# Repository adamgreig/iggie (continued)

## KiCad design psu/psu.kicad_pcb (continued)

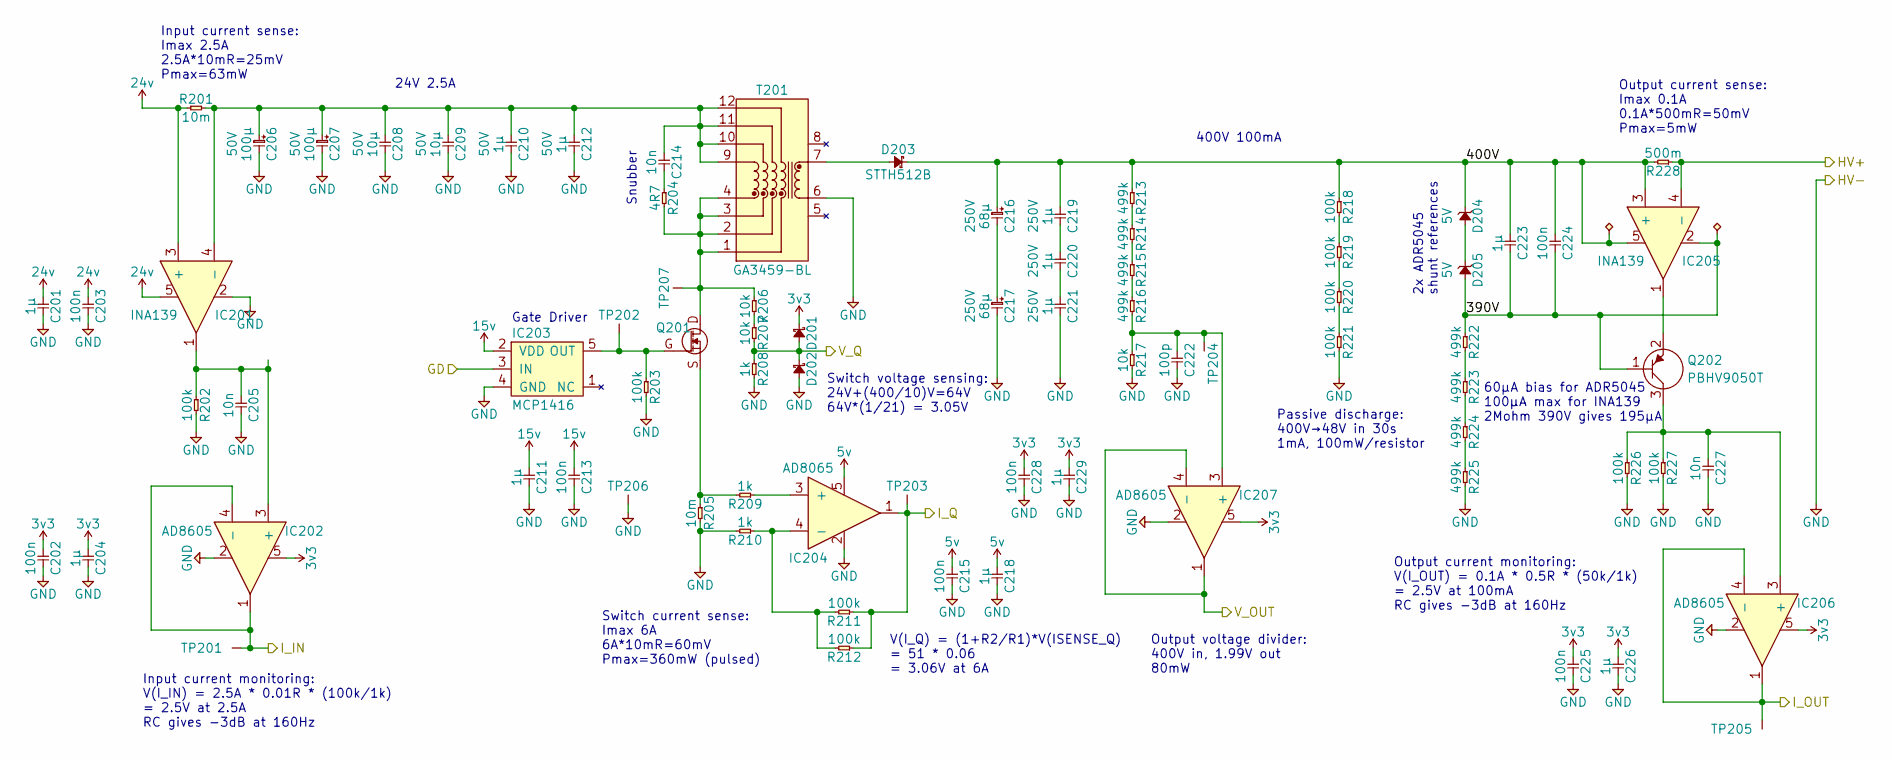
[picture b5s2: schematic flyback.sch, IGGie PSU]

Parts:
C201, C210, C211, C212: 1µ; 1206; Voltage 50V; Farnell 1759454
C202, C203, C213, C215, C224, C225, C228: 100n; 0603; Voltage 50V; Farnell 2320803
C204, C218, C223, C226, C229: 1µ; 0603; Voltage 16V; Farnell 2320814
C205, C227: 10n; 0805; Voltage 25V; Farnell 1457736
C206, C207: 100µ; PANASONIC-SMDCAP-G; Voltage 50V; Farnell 2079271
C208, C209: 10µ; 1210; Voltage 50V; Farnell 2781426
C214: 10n; 1206; Voltage 50V; Farnell 2896776
C216, C217: 68µ; PANASONIC-SMDCAP-K; Voltage 250V; Farnell 2326343
C219, C220, C221: 1µ; 2220; Voltage 250V; Farnell 1828845
C222: 100p; 0603; Voltage 50V; Farnell 9406115
D201, D202: NTS245SFT1G; SOD-123; Farnell 2473418
D203: STTH512B; DPAK_DIODE; Farnell 2344055
D204, D205: ADR5045; SOT-23; Voltage 5V; Farnell 2460166
IC201, IC205: INA139; SOT-23-5; Farnell 1470398
IC202, IC206, IC207: AD8605; SOT-23-5; Farnell 1838870
IC203: MCP1416; SOT-23-5; Farnell 1630421
IC204: AD8065; SOT-23-5; Farnell 2376729
Q201: STB45N60DM2AG; D2PAK_GDS; Farnell 3129762
Q202: PBHV9050T; SOT-23; Voltage 500V; Farnell 1829318
R201, R205: 10m; 1206; Farnell 2079442
R202, R203, R211, R212, R226, R227: 100k; 0603; Voltage 50V; Farnell 2447226
R204: 4R7; 1206; Voltage 50V; Farnell 2447524
R206, R207, R217: 10k; 0603; Voltage 50V; Farnell 2447230
R208, R209, R210: 1k; 0603; Voltage 50V; Farnell 2447272
R213, R214, R215, R216, R222, R223, R224, R225: 499k; 1206; Voltage 200V; Farnell 2695162
R218, R219, R220, R221: 100k; 1206; Voltage 200V; Farnell 2447453
R228: 500m; 1206; Farnell 1717875
T201: GA3459-BL; Farnell 2458040
TP201, TP204, TP205: TESTPAD
TP202, TP203, TP206, TP207: TESTPAD; KEYSTONE5016

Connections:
3v3: C202.1, C204.1, C225.1, C226.1, C228.1, C229.1, D201.1, IC202.5, IC206.5, IC207.5; also elsewhere on the board
5v: C215.1, C218.1, IC204.5; also elsewhere on the board
15v: C211.1, C213.1, IC203.2 (VDD); also elsewhere on the board
24v: C201.1, C203.1, IC201.3 (+), IC201.5, R201.1; also elsewhere on the board
/Flyback/390V: C223.2, C224.2, D205.2, IC205.2, Q202.1 (B), R222.1
/Flyback/400V: C216.2, C219.1, C223.1, C224.1, D203.1, D204.1, IC205.3 (+), IC205.5, R213.1, R218.1, R228.2
/Flyback/HV+: IC205.4 (-), R228.1; also elsewhere on the board
/GD: IC203.3 (IN); also elsewhere on the board
/I_IN: IC202.1, IC202.4 (-), TP201.1; also elsewhere on the board
/I_OUT: IC206.1, IC206.4 (-), TP205.1; also elsewhere on the board
/I_Q: IC204.1, R211.1, R212.1, TP203.1; also elsewhere on the board
/VOUT_MON: IC207.1, IC207.4 (-); also elsewhere on the board
/V_Q: D201.2, D202.1, R207.2, R208.1; also elsewhere on the board
GND: C201.2, C202.2, C203.2, C204.2, C205.2, C206.1, C207.1, C208.2, C209.2, C210.2, C211.2, C212.2, C213.2, C215.2, C217.1, C218.2, C221.2, C222.2, C225.2, C226.2, C227.2, C228.2, C229.2, D202.2, IC201.2, IC202.2, IC203.4 (GND), IC204.2, IC206.2, IC207.2, R202.2, R203.2, R205.2, R208.2, R210.2, R217.2, R221.2, R225.2, R226.2, R227.2, T201.6, TP206.1; also elsewhere on the board
unnamed: C205.1, IC201.1, IC202.3 (+), R202.1
unnamed: C206.2, C207.2, C208.1, C209.1, C210.1, C212.1, C214.1, IC201.4 (-), R201.2, T201.9, T201.10, T201.11, T201.12
unnamed: C214.2, R204.1
unnamed: C216.1, C217.2
unnamed: C219.2, C220.1
unnamed: C220.2, C221.1
unnamed: C222.1, IC207.3 (+), R216.2, R217.1, TP204.1
unnamed: C227.1, IC206.3 (+), Q202.3 (C), R226.1, R227.1
unnamed: D203.2, T201.7
unnamed: D204.2, D205.1
unnamed: IC203.5 (OUT), Q201.G, R203.1, TP202.1
unnamed: IC204.3 (+), R209.1
unnamed: IC204.4 (-), R210.1, R211.2, R212.2
unnamed: IC205.1, Q202.2 (E)
unnamed: Q201.D, R204.2, R206.1, T201.1, T201.2, T201.3, T201.4, TP207.1
unnamed: Q201.S, R205.1, R209.2
unnamed: R206.2, R207.1
unnamed: R213.2, R214.1
unnamed: R214.2, R215.1
unnamed: R215.2, R216.1
unnamed: R218.2, R219.1
unnamed: R219.2, R220.1
unnamed: R220.2, R221.1
unnamed: R222.2, R223.1
unnamed: R223.2, R224.1
unnamed: R224.2, R225.1

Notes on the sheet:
Switch current sense: Imax 6A 6A*10mR=60mV Pmax=360mW (pulsed)
Snubber
Passive discharge: 400V→48V in 30s 1mA, 100mW/resistor
Gate Driver
V(I_Q) = (1+R2/R1)*V(ISENSE_Q) = 51 * 0.06 = 3.06V at 6A
Input current monitoring: V(I_IN) = 2.5A * 0.01R * (100k/1k) = 2.5V at 2.5A RC gives -3dB at 160Hz
Output voltage divider: 400V in, 1.99V out 80mW
Output current monitoring: V(I_OUT) = 0.1A * 0.5R * (50k/1k) = 2.5V at 100mA RC gives -3dB at 160Hz
60µA bias for ADR5045 100µA max for INA139 2Mohm 390V gives 195µA
2x ADR5045 shunt references
24V 2.5A
400V 100mA
Switch voltage sensing: 24V+(400/10)V=64V 64V*(1/21) = 3.05V
Input current sense: Imax 2.5A 2.5A*10mR=25mV Pmax=63mW
Output current sense: Imax 0.1A 0.1A*500mR=50mV Pmax=5mW

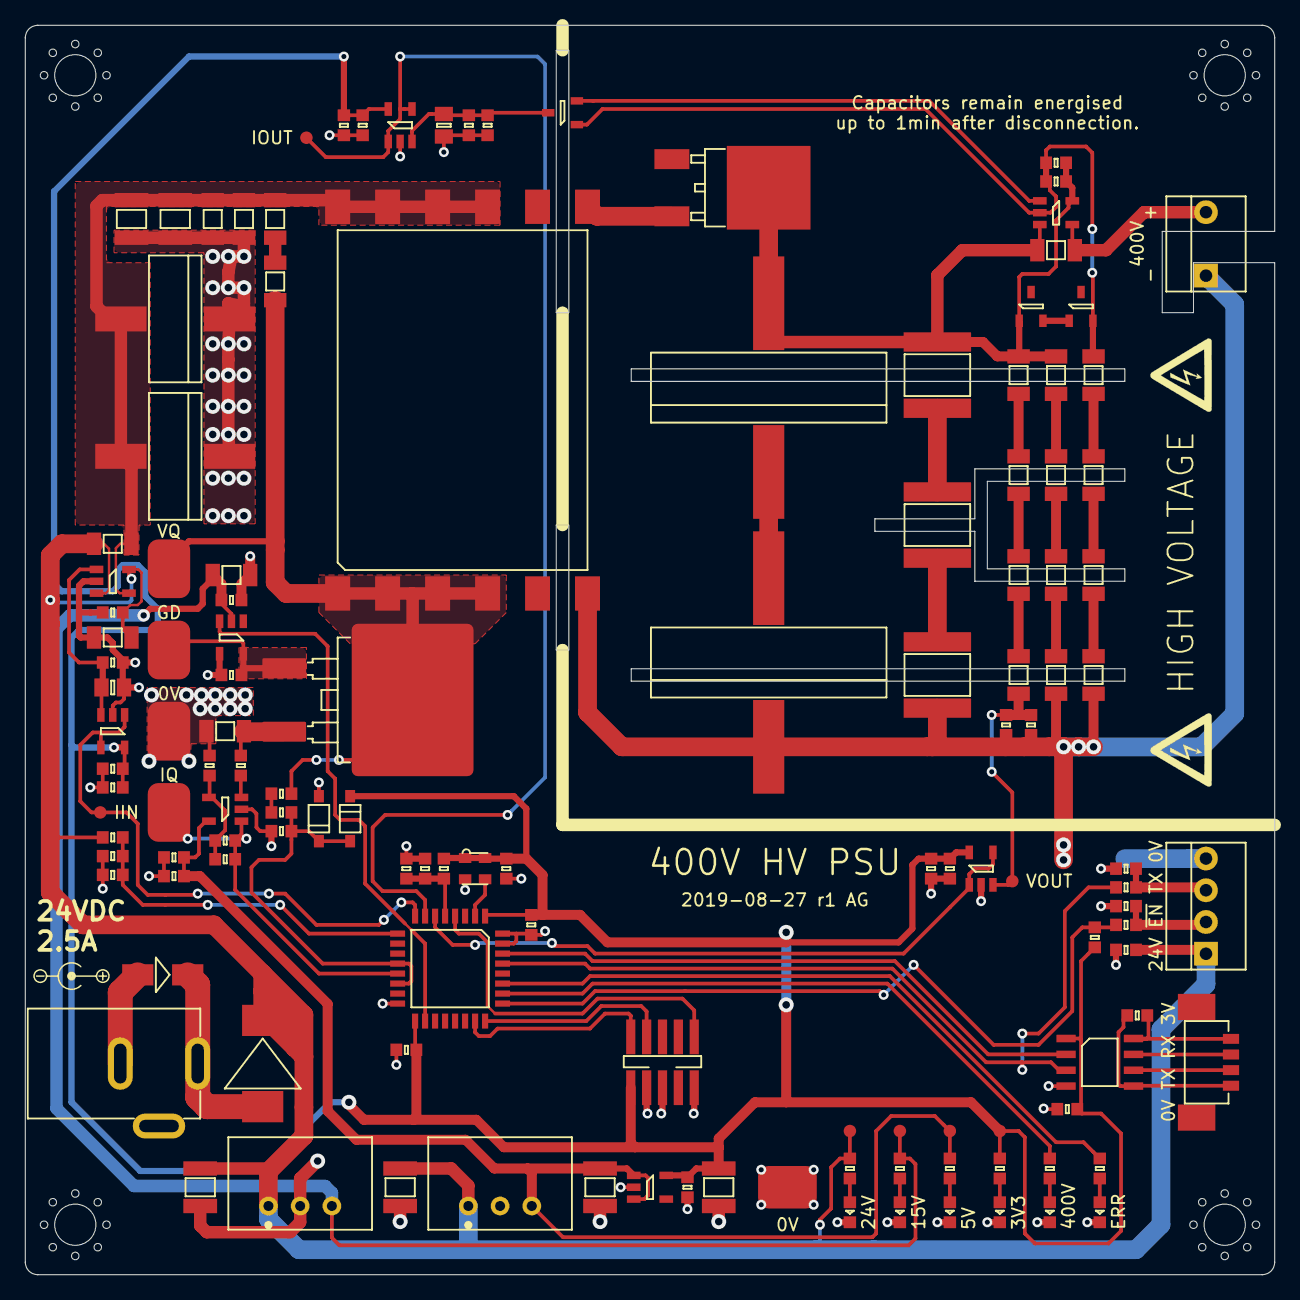
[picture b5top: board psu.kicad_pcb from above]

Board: 2 copper layers, 100.0 x 100.0 mm, 137 parts (0 on the bottom side), 64 nets.

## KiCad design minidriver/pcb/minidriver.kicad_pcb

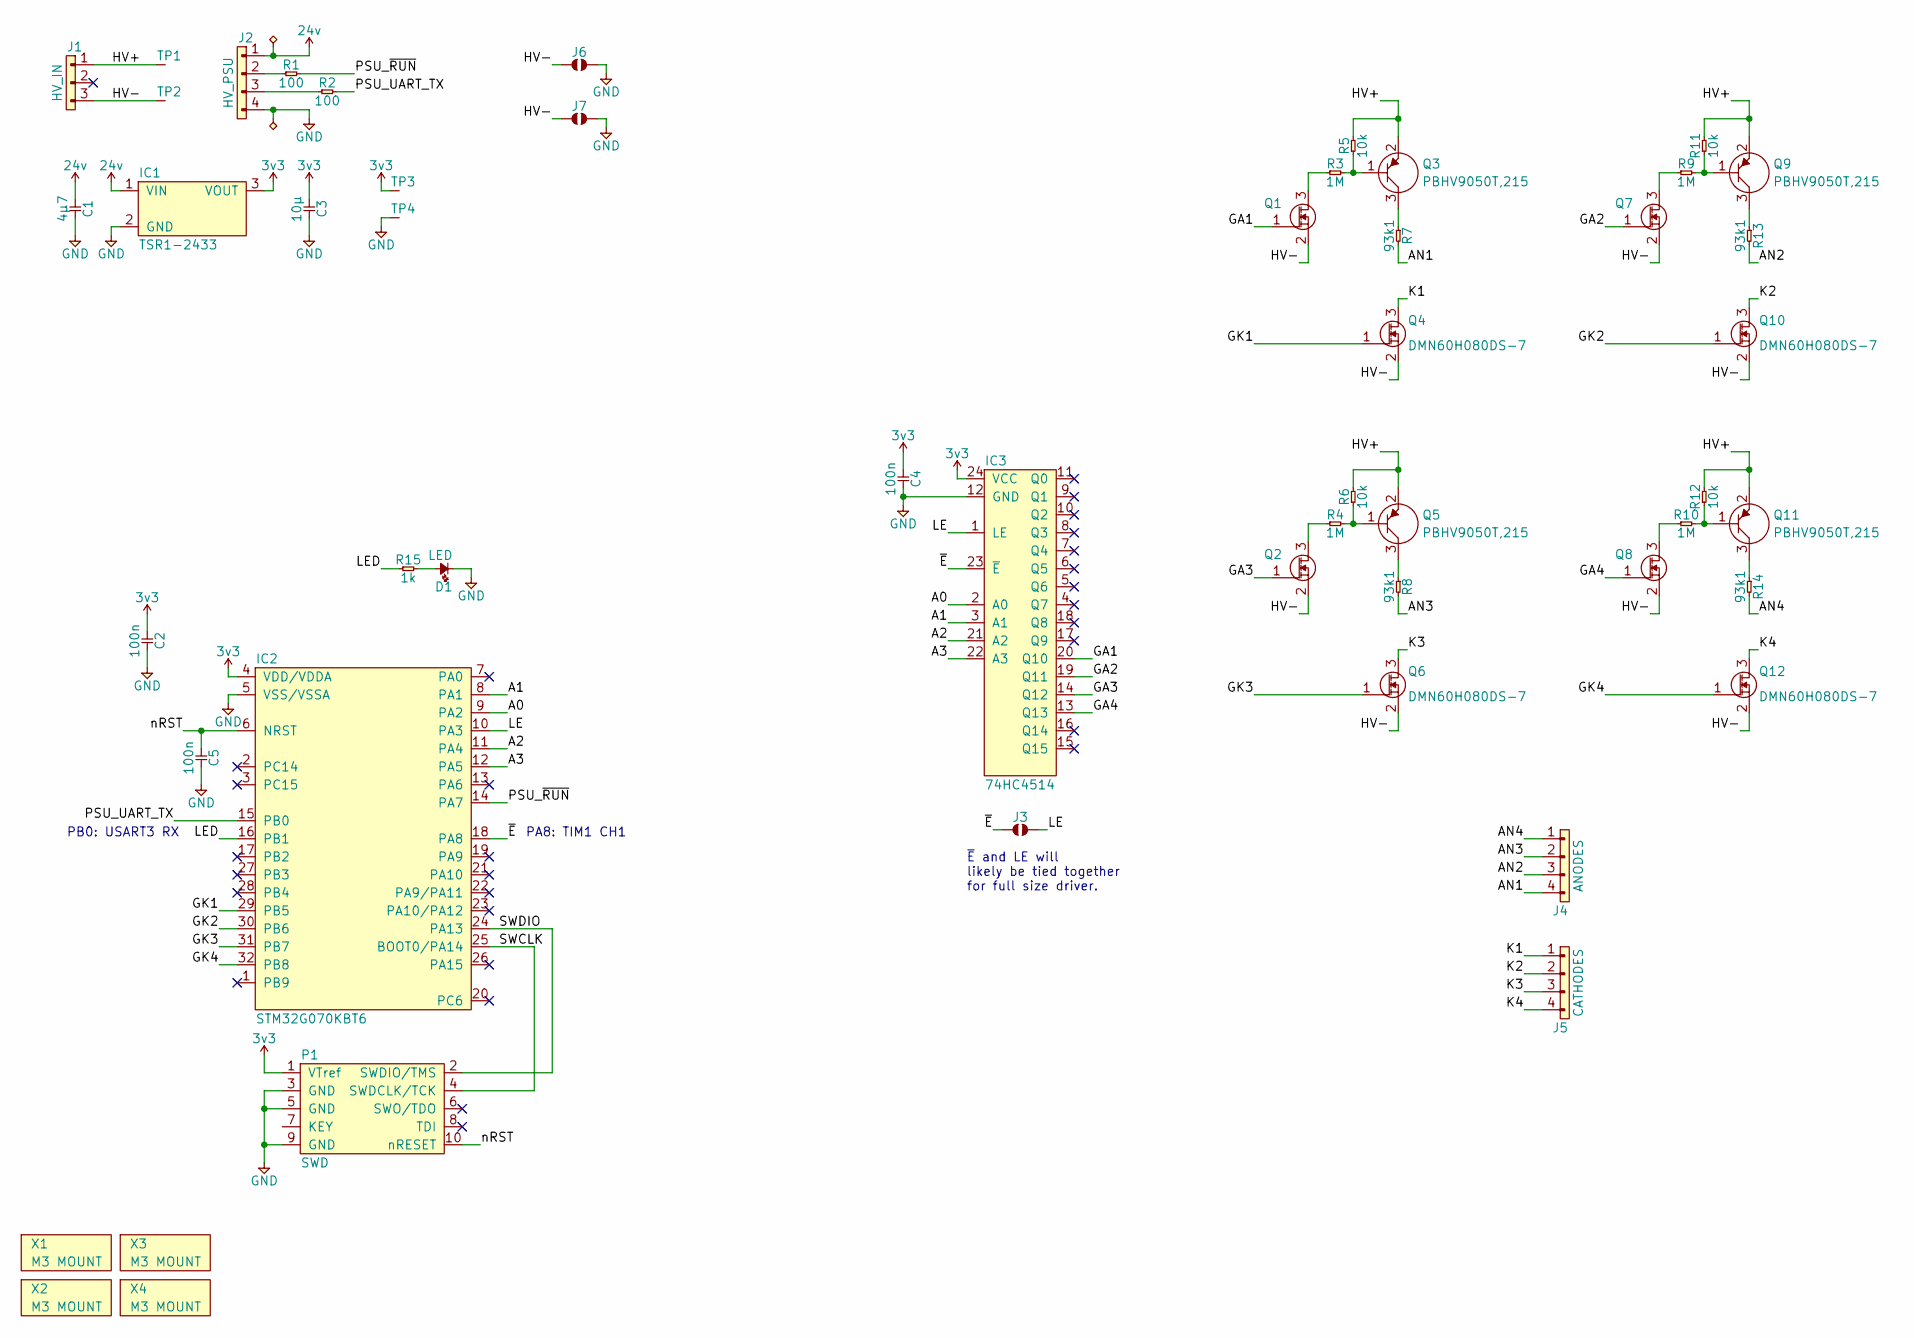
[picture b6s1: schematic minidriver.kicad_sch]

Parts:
C1: 4µ7; 1206; Voltage 50V; Farnell 2112859
C2, C4, C5: 100n; 0402; Voltage 16V; Farnell 2810260
C3: 10µ; 0603; Voltage 6.3V; Farnell 3013391
D1: LED; 0603-LED; Farnell 2290328
IC1: TSR1-2433; TSR1; Farnell 1696319
IC2: STM32G070KBT6; LQFP-32; Farnell 3365394
IC3: 74HC4514; SOIC-24-W; Farnell 2444987
J1: HV_IN; MOLEX-KK-254P-03; Farnell 1360131
J2: HV_PSU; MOLEX-KK-254P-04; Farnell 1360132
J3, J6, J7: SJ2
J4: ANODES; MOLEX-KK-254P-04; Farnell 1360132
J5: CATHODES; MOLEX-KK-254P-04; Farnell 1360132
P1: SWD; FTSH-105-01-L-DV-K; Farnell 2856437
Q1, Q2, Q4, Q6, Q7, Q8, Q10, Q12: DMN60H080DS-7; SOT-23; Farnell 3127344
Q3, Q5, Q9, Q11: PBHV9050T,215; SOT-23; Farnell 1829318
R1, R2: 100; 0402; Voltage 50V; Farnell 9239111
R3, R4, R9, R10: 1M; 1206; Voltage 500V; Farnell 1750877
R5, R6, R11, R12: 10k; 1206; Voltage 500V; Farnell 1750850
R7, R8, R13, R14: 93k1; 1206; Voltage 500V; Farnell 2327389
R15: 1k; 0402; Voltage 50V; Farnell 2331474
TP1, TP2: TESTPAD; KEYSTONE5016; Farnell 2292858
TP3: TESTPAD
TP4: TESTPAD; SIL-254P-01
X1, X2, X3, X4: M3 MOUNT; M3_MOUNT

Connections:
3v3: C2.1, C3.1, C4.1, IC1.3 (VOUT), IC2.4 (VDD/VDDA), IC3.24 (VCC), P1.1 (VTref), TP3.1 (TP)
24v: C1.1, IC1.1 (VIN), J2.1
/A0: IC2.9 (PA2), IC3.2 (A0)
/A1: IC2.8 (PA1), IC3.3 (A1)
/A2: IC2.11 (PA4), IC3.21 (A2)
/A3: IC2.12 (PA5), IC3.22 (A3)
/AN1: J4.4, R7.2
/AN2: J4.3, R13.2
/AN3: J4.2, R8.2
/AN4: J4.1, R14.2
/GA1: IC3.20 (Q10), Q1.1 (G)
/GA2: IC3.19 (Q11), Q7.1 (G)
/GA3: IC3.14 (Q12), Q2.1 (G)
/GA4: IC3.13 (Q13), Q8.1 (G)
/GK1: IC2.29 (PB5), Q4.1 (G)
/GK2: IC2.30 (PB6), Q10.1 (G)
/GK3: IC2.31 (PB7), Q6.1 (G)
/GK4: IC2.32 (PB8), Q12.1 (G)
/HV+: J1.1, Q3.2 (E), Q5.2 (E), Q9.2 (E), Q11.2 (E), R5.2, R6.2, R11.2, R12.2, TP1.1 (TP)
/HV-: J1.3, J6.1, J7.1, Q1.2 (S), Q2.2 (S), Q4.2 (S), Q6.2 (S), Q7.2 (S), Q8.2 (S), Q10.2 (S), Q12.2 (S), TP2.1 (TP)
/K1: J5.1, Q4.3 (D)
/K2: J5.2, Q10.3 (D)
/K3: J5.3, Q6.3 (D)
/K4: J5.4, Q12.3 (D)
/LE: IC2.10 (PA3), IC3.1 (LE), J3.2
/LED: IC2.16 (PB1), R15.1
/PSU_UART_TX: IC2.15 (PB0), R2.2
/PSU_~RUN: IC2.14 (PA7), R1.2
/SWCLK: IC2.25 (BOOT0/PA14), P1.4 (SWDCLK/TCK)
/SWDIO: IC2.24 (PA13), P1.2 (SWDIO/TMS)
/nRST: C5.1, IC2.6 (NRST), P1.10 (nRESET)
/~E: IC2.18 (PA8), IC3.23 (~E), J3.1
GND: C1.2, C2.2, C3.2, C4.2, C5.2, D1.1, IC1.2 (GND), IC2.5 (VSS/VSSA), IC3.12 (GND), J2.4, J6.2, J7.2, P1.3 (GND), P1.5 (GND), P1.9 (GND), TP4.1 (TP)
unnamed: D1.2, R15.2
unnamed: J2.2, R1.1
unnamed: J2.3, R2.1
unnamed: Q1.3 (D), R3.1
unnamed: Q2.3 (D), R4.1
unnamed: Q3.1 (B), R3.2, R5.1
unnamed: Q3.3 (C), R7.1
unnamed: Q5.1 (B), R4.2, R6.1
unnamed: Q5.3 (C), R8.1
unnamed: Q7.3 (D), R9.1
unnamed: Q8.3 (D), R10.1
unnamed: Q9.1 (B), R9.2, R11.1
unnamed: Q9.3 (C), R13.1
unnamed: Q11.1 (B), R10.2, R12.1
unnamed: Q11.3 (C), R14.1
no_connect_49: IC2.1 (PB9)
no_connect_50: IC2.13 (PA6)
no_connect_51: IC2.17 (PB2)
no_connect_52: IC2.19 (PA9)
no_connect_53: IC2.2 (PC14)
no_connect_54: IC2.20 (PC6)
no_connect_55: IC2.21 (PA10)
no_connect_56: IC2.22 (PA9/PA11)
no_connect_57: IC2.23 (PA10/PA12)
no_connect_58: IC2.26 (PA15)
no_connect_59: IC2.27 (PB3)
no_connect_60: IC2.28 (PB4)
no_connect_61: IC2.3 (PC15)
no_connect_62: IC2.7 (PA0)
no_connect_63: IC3.10 (Q2)
no_connect_64: IC3.11 (Q0)
no_connect_65: IC3.15 (Q15)
no_connect_66: IC3.16 (Q14)
no_connect_67: IC3.17 (Q9)
no_connect_68: IC3.18 (Q8)
no_connect_69: IC3.4 (Q7)
no_connect_70: IC3.5 (Q6)
no_connect_71: IC3.6 (Q5)
no_connect_72: IC3.7 (Q4)
no_connect_73: IC3.8 (Q3)
no_connect_74: IC3.9 (Q1)
no_connect_76: P1.6 (SWO/TDO)
no_connect_77: P1.8 (TDI)

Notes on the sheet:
PB0: USART3 RX
PA8: TIM1 CH1
~E~ and LE will likely be tied together for full size driver.

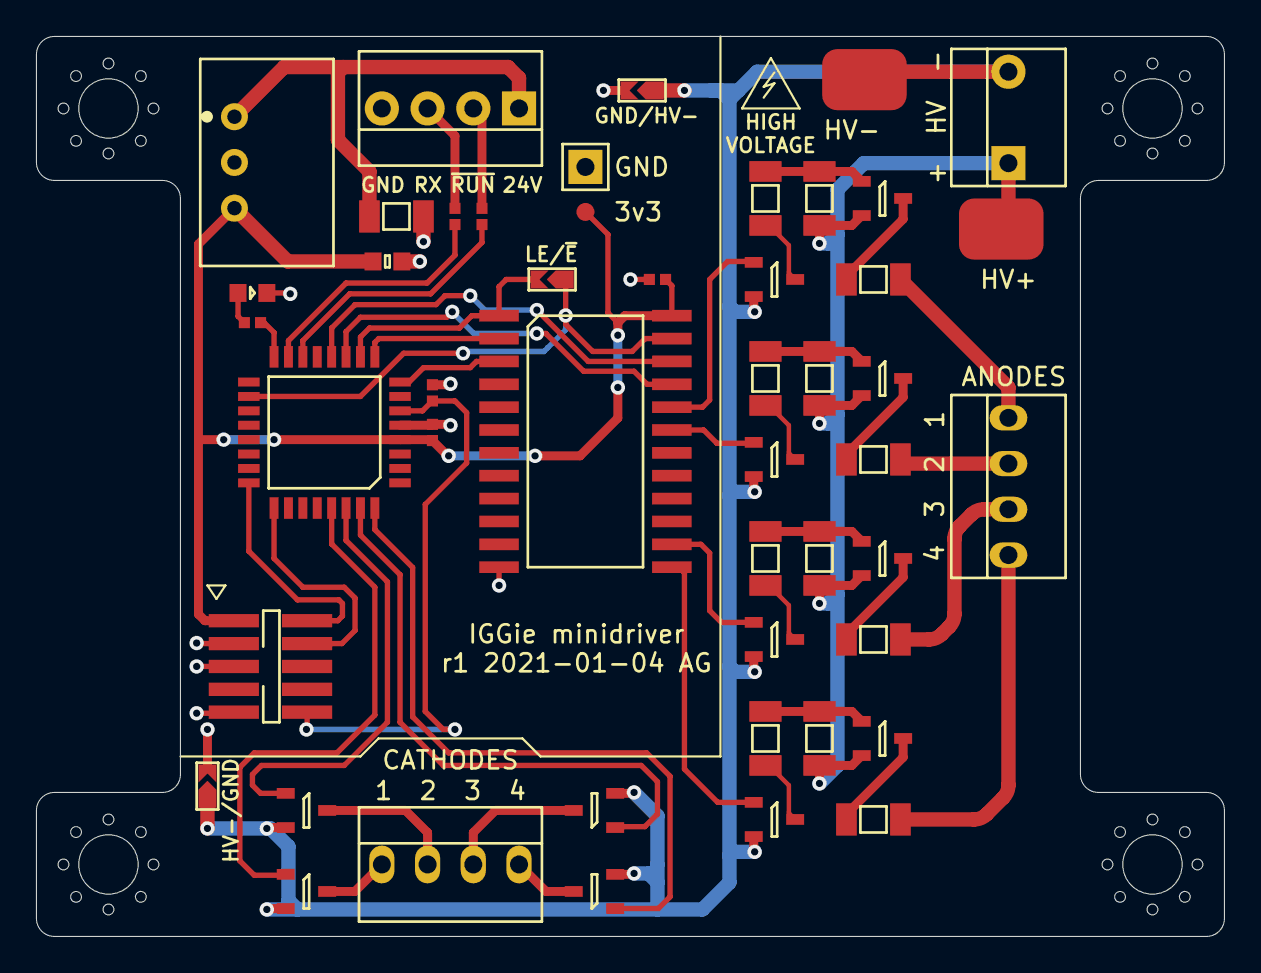
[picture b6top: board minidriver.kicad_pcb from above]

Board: 2 copper layers, 66.0 x 50.0 mm, 52 parts (0 on the bottom side), 48 nets.

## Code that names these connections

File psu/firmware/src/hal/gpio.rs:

use stm32ral::{gpio, modify_reg, write_reg, read_reg};

pub struct GPIO {
    gpioa: gpio::Instance,
    gpiob: gpio::Instance,
}

impl GPIO {
    pub fn new(gpioa: gpio::Instance, gpiob: gpio::Instance) -> Self {
        GPIO { gpioa, gpiob }
    }

    pub fn setup(&self) {
        let gpioa = &self.gpioa;
        let gpiob = &self.gpiob;

        // Set PA8 GD to HRTIM CHA1
        modify_reg!(stm32ral::gpio, gpioa, ODR, ODR8: 0);
        modify_reg!(stm32ral::gpio, gpioa, OSPEEDR, OSPEEDR8: HighSpeed);
        modify_reg!(stm32ral::gpio, gpioa, AFRH, AFRH8: AF13);
        modify_reg!(stm32ral::gpio, gpioa, MODER, MODER8: Alternate);

        // Set both LEDs to outputs
        modify_reg!(stm32ral::gpio, gpiob, MODER, MODER3: Output, MODER4: Output);
        modify_reg!(stm32ral::gpio, gpiob, ODR, ODR3: 0, ODR4: 0);

        // Set PB6 to USART Tx (AF7)
        modify_reg!(stm32ral::gpio, gpiob, AFRL, AFRL6: AF7);
        modify_reg!(stm32ral::gpio, gpiob, MODER, MODER6: Alternate);

        // Set PA0, 1, 2, 3, 6, 7 to analogue input for ADCs and COMPs
        modify_reg!(stm32ral::gpio, gpioa, MODER, MODER0: Analog, MODER1: Analog, MODER2: Analog,
                                                  MODER3: Analog, MODER6: Analog, MODER7: Analog);

        // Set PB0 to analogue input for COMP4
        modify_reg!(stm32ral::gpio, gpiob, MODER, MODER0: Analog);

        // Set PA15 to HRTIM1_FLT2 for fault detection
        modify_reg!(stm32ral::gpio, gpioa, AFRH, AFRH15: AF13);
        modify_reg!(stm32ral::gpio, gpioa, MODER, MODER15: Alternate);

        // Prototyping COMP and DAC outputs:

        // Set COMP2 output to PA12 for prototyping
        modify_reg!(stm32ral::gpio, gpioa, AFRH, AFRH12: AF8);
        modify_reg!(stm32ral::gpio, gpioa, MODER, MODER12: Alternate);

        // Set COMP4 output to PB1 for prototyping
        modify_reg!(stm32ral::gpio, gpiob, AFRL, AFRL1: AF8);
        modify_reg!(stm32ral::gpio, gpiob, MODER, MODER1: Alternate);

        // Set DAC1_OUT1 output to PA4 for prototyping
        modify_reg!(stm32ral::gpio, gpioa, MODER, MODER4: Analog);

        // Set DAC1_OUT2 output to PA5 for prototyping
        modify_reg!(stm32ral::gpio, gpioa, MODER, MODER5: Analog);
    }

    pub fn set_400v_led(&self, state: bool) {
        if state {
            write_reg!(stm32ral::gpio, self.gpiob, BSRR, BS3: Set);
        } else {
            write_reg!(stm32ral::gpio, self.gpiob, BSRR, BR3: Reset);
        }
    }

    pub fn set_err_led(&self, state: bool) {
        if state {
            write_reg!(stm32ral::gpio, self.gpiob, BSRR, BS4: Set);
        } else {
            write_reg!(stm32ral::gpio, self.gpiob, BSRR, BR4: Reset);
        }
    }

    pub fn get_run(&self) -> bool {
        read_reg!(stm32ral::gpio, self.gpioa, IDR, IDR15 == Low)
    }

    pub unsafe fn global_set_err_led() {
        write_reg!(stm32ral::gpio, GPIOB, BSRR, BS4: Set);
    }
}

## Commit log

2018-02-13 begin rough work on psu
2018-02-13 spec most parts
2018-02-14 add some TPs etc
2019-07-22 Redraw PSU
2019-07-23 continued updates on psu
2019-07-24 update psu
2019-07-24 assign diodes and main transistors
2019-07-26 Select main L and C
2019-07-29 Update current sense Rs
2019-08-23 update before swapping to flyback
2019-08-26 Stop work on 2stage boost, swap to new flyback design
2019-08-26 Annotate
2019-08-27 Start PCB
2019-08-27 More PCB
2019-08-28 More pcb layout
2019-08-29 routing
2019-09-01 Complete routing. But maybe the transformer is the wrong way around.
2019-09-05 Complete routing take 2, with transformer secondary pins swapped
2019-09-05 Reposition HV resistor chains
2019-09-05 Tidy up tracks. RFM r1.
2019-09-12 Update Farnell part numbers
2019-09-12 Add load PCB
2019-09-24 Start work on driver PCB
2019-09-27 Finish sch, start PCB
2019-10-04 WIP PCB
2019-10-10 Start work on 32ch board
2019-10-11 more layout work
2019-10-14 WIP routing driver
2019-10-21 move pcbs into subfolders
2019-10-21 start fw ish
2019-10-21 Fix paths in lib tables
2019-10-21 Try RTFM
2019-10-23 WIP firmware
2019-11-06 Working USART telemetry via DMA
2019-11-07 Working ADC and DMA out via telem
2019-11-10 hrtim driver, working very basic regulation
2019-11-13 vq detection and fault handling
2019-11-19 working at 20W 400V...
2019-12-04 kalman filter, pid, rename telem to state, ..
2019-12-05 try out new pid control
2019-12-05 remove i_thresh, tune pid
2019-12-18 update fault handling
2019-12-19 update telem script spacing
2019-12-19 remove semihosting panic
2019-12-20 Remove old hprintln
2019-12-29 Update voltage setpoint for panel operation at 370V
2020-03-15 Update stm32ral to 0.4.1 for psu fw
2020-05-23 Fix typo in comment
2020-05-26 Update to use HRTIM burst mode, variable duty cycle at low loads. Also removes VQ and IQ ADC sampling as it was unused.
2020-05-26 Tune Kalman filters (and increase telem baud to 3.5M)
2020-05-27 Update PID gains
2020-07-15 Start driver2
2020-07-15 Fix typo in Kalman filter comments
2020-07-20 Update dependencies to latest versions
2020-07-20 Update to cortex-m-rtic
2021-01-03 Disable HRTIM fault interrupt when disabling HRTIM, re-enable when enabling HRTIM
2021-01-03 Move old driver/ to driver0/
2021-01-03 Update agg-kicad submodule
2021-01-04 Add minidriver
2021-01-16 add initial firmware for minidriver
2021-01-17 fw now draws frames ok
2021-01-18 Bump setpoint to 375V
2021-01-18 Update minidriver fw
2021-03-18 move minidriver pcb into pcb folder
2021-03-18 add hss and lss pmods
